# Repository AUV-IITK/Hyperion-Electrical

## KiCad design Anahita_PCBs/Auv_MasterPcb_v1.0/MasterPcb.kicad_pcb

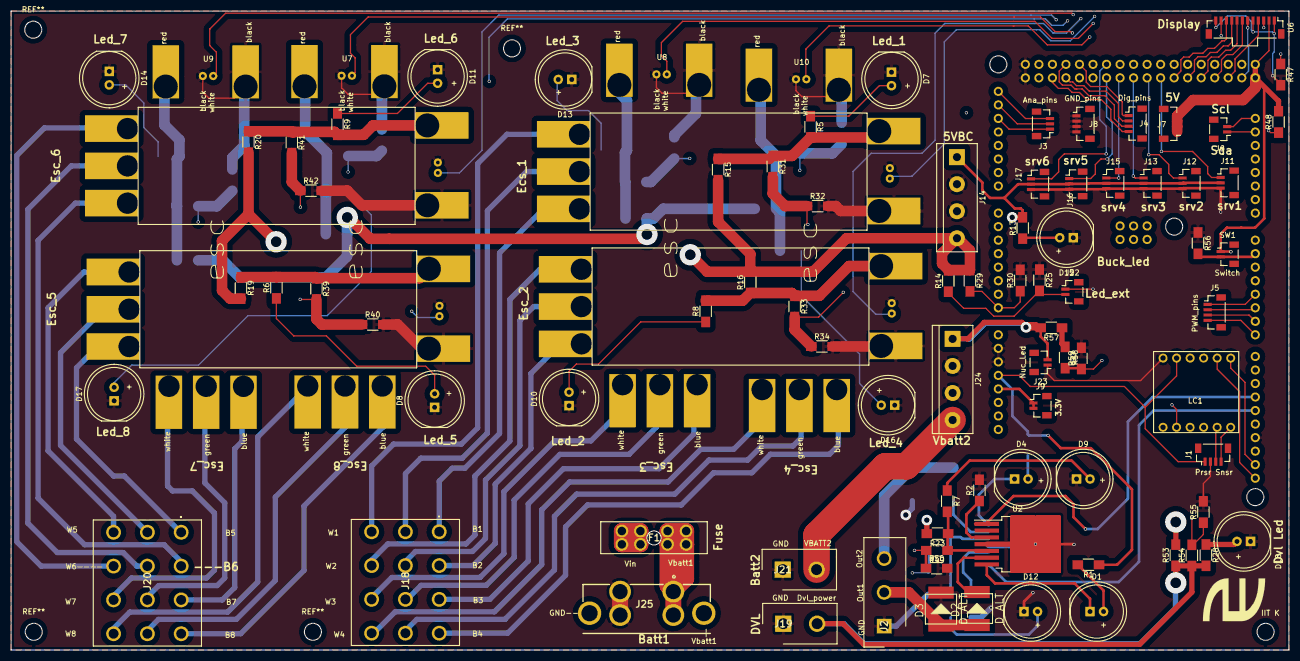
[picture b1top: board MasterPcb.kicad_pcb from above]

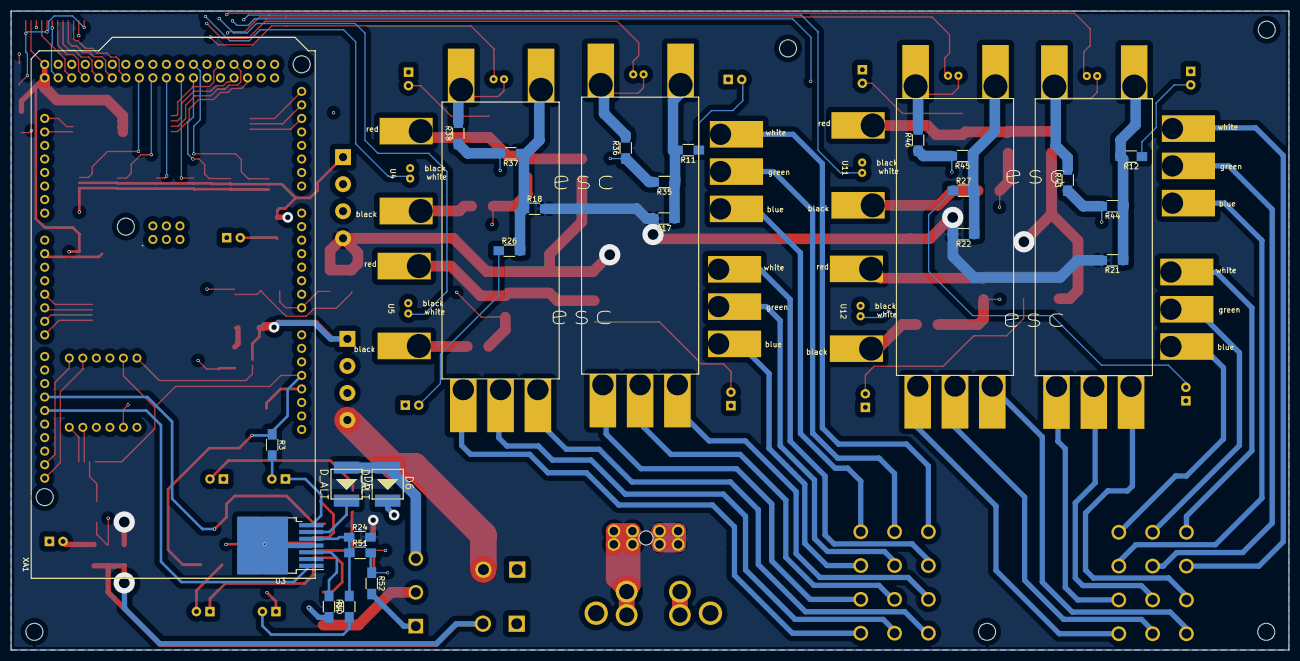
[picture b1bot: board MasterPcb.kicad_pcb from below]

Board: 4 copper layers, 240.0 x 120.0 mm, 118 parts (30 on the bottom side), 122 nets.

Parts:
D1, D4, D7, D8, D9, D10, D11, D12, D13, D14, D15, D16, D17, D18: LED; LED_D10.0mm
D2, D3, D5, D6: D_ALT; DO-214AB
F1: Fuse
IIT K: LOGO; logo
IIT K#2: M1; MountingHole_3.2mm_M3_DIN965
J1: Conn_02x02_Counter_Clockwise; Molex_PicoClasp_501331-0407_1x04_P1.0mm_Vertical
J2: conn_01x03; 1_3 pin&socket
J3: Conn_01x03_Male; Molex_PicoClasp_501331-0307_1x03_P1.0mm_Vertical
J4, J5, J7, J8: Conn_01x04_Male; Molex_PicoClasp_501331-0407_1x04_P1.0mm_Vertical
J6, J9: Conn_01x02_Male; Molex_PicoClasp_501331-0207_1x02_P1.0mm_Vertical
J11, J12, J13, J15, J16, J17: Conn_01x03_servo; Molex_PicoClasp_501331-0307_1x03_P1.0mm_Vertical
J14: Conn_01x04_5V_buckconverter; TerminalBlock_bornier-4_P5.08mm
J18, J20: Conn_01x12; 4_3connector
J19: Conn_01x02_Male_dvl; 1x2_Conn_
J21: Conn_01x02_power_nuc; 1x2_Conn_
J22: Led_ext_conn; Molex_PicoClasp_501331-0207_1x02_P1.0mm_Vertical
J23: Led_ext_nuc_conn; Molex_PicoClasp_501331-0207_1x02_P1.0mm_Vertical
J24: Conn_01x04_nuc_buck; TerminalBlock_bornier-4_P5.08mm
J25: Conn_01x04_power; power
LC1: Logic_Converter
R1, R3: 5K; R_1206_HandSoldering
R2, R4: 4K; R_1206_HandSoldering
R5, R6, R7, R8, R9, R10, R11, R12, R13, R26, R27, R28, R30, R32, R34, R36, R38, R40, R42, R43, R46, R47, R50, R52, R55, R56, R59: 1K; R_1206_HandSoldering
R14: 1k; R_1206_HandSoldering
R15, R16, R17, R18, R19, R20, R21, R22, R23, R24, R53, R57: 50m; R_1206_HandSoldering
R25: 4k; R_1206_HandSoldering
R29, R31, R33, R35, R37, R39, R41, R44, R45, R49, R51, R54, R58: 24K; R_1206_HandSoldering
R48: 220; R_1206_HandSoldering
SW1: SW_DIP_x01; Molex_PicoClasp_501331-0207_1x02_P1.0mm_Vertical
U2, U3: DRV102-RESCUE-Actuator_board; TO-263-7_TabPin4
U4, U5, U11, U12: ESCPINS; esc_redefined
U6: DS1; Molex_PicoClasp_501331-1207_1x12_P1.0mm_Vertical
U7, U8, U9, U10: ESCPINS; esc_mirror_redefined
XA1: Arduino_Mega2560_Shield

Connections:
/3.3V: J9.1, J9.2, LC1.8, XA1.3V3
/5V: J1.1, J7.1, J7.2, J7.3, J7.4, LC1.2, R1.1, R3.1, R48.2, SW1.1, U6.2, XA1.5V1, XA1.5V3, XA1.5V4
/5VBC: J11.2, J12.2, J13.2, J14.1, J15.2, J16.2, J17.2, R13.2
/22: U6.6, XA1.D22
/24: U6.4, XA1.D24
/26: U6.7, XA1.D26
/28: U6.8, XA1.D28
/30: U6.9, XA1.D30
/32: U6.10, XA1.D32
/A0: R29.2, R30.1, XA1.A0
/A1: R31.2, R32.1, XA1.A1
/A2: R33.2, R34.1, XA1.A2
/A3: R35.2, R36.1, XA1.A3
/A4: R37.2, R38.1, XA1.A4
/A5: R39.2, R40.1, XA1.A5
/A6: R41.2, R42.1, XA1.A6
/A7: R43.1, R44.2, XA1.A7
/A8: R45.2, R46.1, XA1.A8
/A9: R49.2, R50.1, XA1.A9
/A10: R51.2, R52.1, XA1.A10
/A11: R54.2, R55.1, XA1.A11
/A12: R58.2, R59.1, XA1.A12
/ANA1: J3.1, XA1.A13
/ANA2: J3.2, XA1.A14
/ANA3: J3.3, XA1.A15
/B1: J18.1, U4.1
/B2: J18.4, U5.1
/B3: J18.7, U8.1
/B4: J18.10, U10.1
/B5: J20.1, U12.1
/B6: J20.4, U11.1
/B7: J20.7, U9.1
/B8: J20.10, U7.1
/DIG1: J4.1, XA1.D47
/DIG2: J4.2, XA1.D48
/DIG3: J4.3, XA1.D49
/DIG4: J4.4, XA1.D50
/DVL: J19.2, R28.2, R53.1, R54.1
/G1: J18.2, U4.2
/G2: J18.5, U5.2
/G3: J18.8, U8.2
/G4: J18.11, U10.2
/G5: J20.2, U12.2
/G6: J20.5, U11.2
/G7: J20.8, U9.2
/G8: J20.11, U7.2
/IN_1: U2.1, XA1.D11
/IN_2: U3.1, XA1.D12
/Led_ext: J22.2, R14.1, R25.2
/Led_ext_nuc: J23.2, J24.1, R57.2
/NUC: R57.1, R58.1
/OUT_1: D2.1, D3.1, J2.2
/OUT_2: D5.1, D6.1, J2.3
/PWM-1: J5.1, XA1.D4
/PWM-2: J5.2, XA1.D5
/PWM-3: J5.3, XA1.D6
/PWM-4: J5.4, XA1.D7
/SCL1: J6.2, XA1.D21
/SCL(HV): LC1.5, XA1.SCL
/SCL(PS): J1.3, LC1.11
/SDA1: J6.1, XA1.D20
/SDA(HV): LC1.6, XA1.SDA
/SDA(PS): J1.4, LC1.12
/SER1: J11.1, XA1.D34
/SER2: J12.1, XA1.D36
/SER3: J13.1, XA1.D38
/SER4: J15.1, XA1.D40
/SER5: J16.1, XA1.D42
/SER6: J17.1, XA1.D43
/SOV1: R7.2, R23.1, R49.1, U2.5
/SOV2: R10.2, R24.1, R51.1, U3.5
/T-1: U4.4, XA1.D23
/T-2: U5.4, XA1.D25
/T-3: U8.4, XA1.D27
/T-4: U10.4, XA1.D29
/T-5: U12.4, XA1.D31
/T-6: U11.4, XA1.D33
/T-7: U9.4, XA1.D35
/T-8: U7.4, XA1.D37
/Trigger: R56.2, SW1.2, XA1.D1
/VBATT1: F1.1, F1.2, F1.3, F1.4, J25.1, J25.2
/VBATT2: J21.2, J24.4
/VESC1: R5.2, R15.1, R31.1, U4.6
/VESC2: R8.2, R16.1, R33.1, U5.6
/VESC3: R11.2, R17.1, R35.1, U8.6
/VESC4: R18.1, R26.2, R37.1, U10.6
/VESC5: R6.2, R19.1, R39.1, U12.6
/VESC6: R9.2, R20.1, R41.1, U11.6
/VESC7: R12.2, R21.1, R44.1, U9.6
/VESC8: R22.1, R27.2, R45.1, U7.6
/VIN1: F1.5, F1.6, F1.7, F1.8, J14.4, R14.2, R15.2, R16.2, R17.2, R18.2, R19.2, R20.2, R21.2, R22.2, R23.2, R24.2, R29.1, R53.2
/W1: J18.3, U4.3
/W2: J18.6, U5.3
/W3: J18.9, U8.3
/W4: J18.12, U10.3
/W5: J20.3, U12.3
/W6: J20.6, U11.3
/W7: J20.9, U9.3
/W8: J20.12, U7.3
GND: D3.2, D6.2, D7.1, D8.1, D9.1, D10.1, D11.1, D12.1, D13.1, D14.1, D15.1, D16.1, D17.1, D18.1, J1.2, J2.1, J8.1, J8.2, J8.3, J8.4, J11.3, J12.3, J13.3, J14.2, J14.3, J15.3, J16.3, J17.3, J19.1, J21.1, J22.1, J23.1, J24.2, J24.3, J25.3, J25.4, LC1.1, R2.2, R4.2, R25.1, R30.2, R32.2, R34.2, R36.2, R38.2, R40.2, R42.2, R43.2, R46.2, R47.2, R50.2, R52.2, R55.2, R56.1, R59.2, U2.4, U3.4, U4.5, U4.7, U5.5, U5.7, U6.1, U6.5, U6.12, U7.5, U7.7, U8.5, U8.7, U9.5, U9.7, U10.5, U10.7, U11.5, U11.7, U12.5, U12.7, XA1.GND1, XA1.GND2, XA1.GND3, XA1.GND5, XA1.GND6
unnamed: D1.1, U2.7
unnamed: D1.2, R1.2
unnamed: D2.2, U2.6
unnamed: D4.1, U3.7
unnamed: D4.2, R3.2
unnamed: D5.2, U3.6
unnamed: D7.2, R5.1
unnamed: D8.2, R6.1
unnamed: D9.2, R7.1
unnamed: D10.2, R8.1
unnamed: D11.2, R9.1
unnamed: D12.2, R10.1
unnamed: D13.2, R11.1
unnamed: D14.2, R12.1
unnamed: D15.2, R13.1
unnamed: D16.2, R26.1
unnamed: D17.2, R27.1
unnamed: D18.2, R28.1
unnamed: R2.1, U2.3
unnamed: R4.1, U3.3
unnamed: R47.1, U6.3
unnamed: R48.1, U6.11

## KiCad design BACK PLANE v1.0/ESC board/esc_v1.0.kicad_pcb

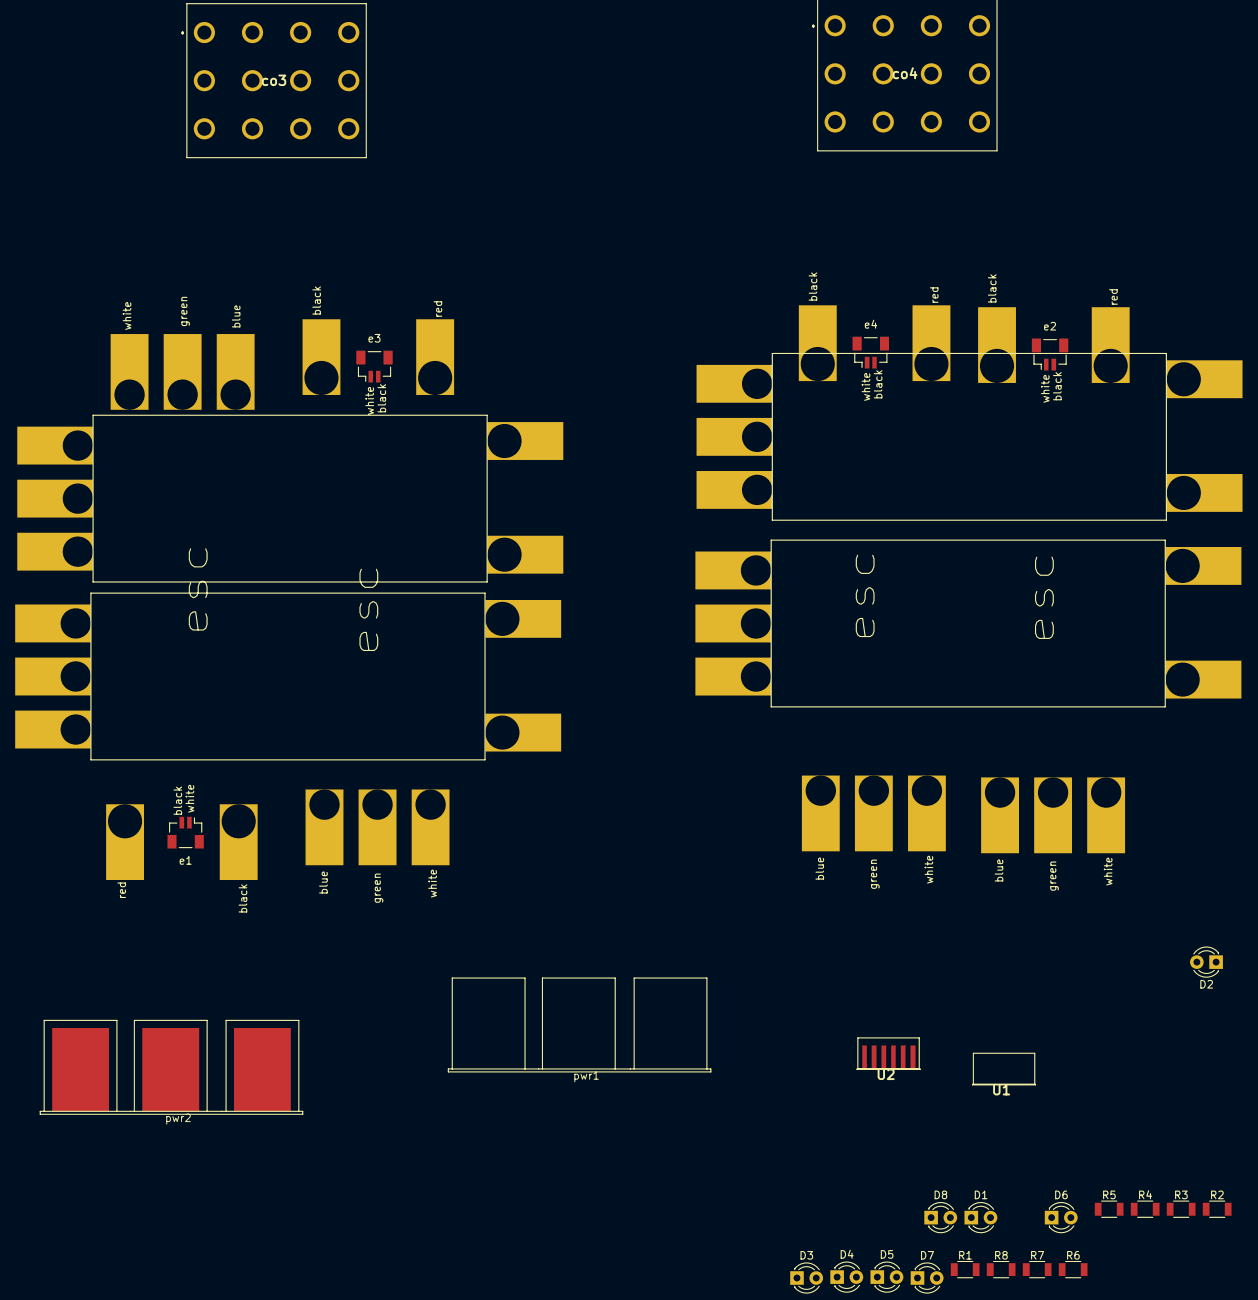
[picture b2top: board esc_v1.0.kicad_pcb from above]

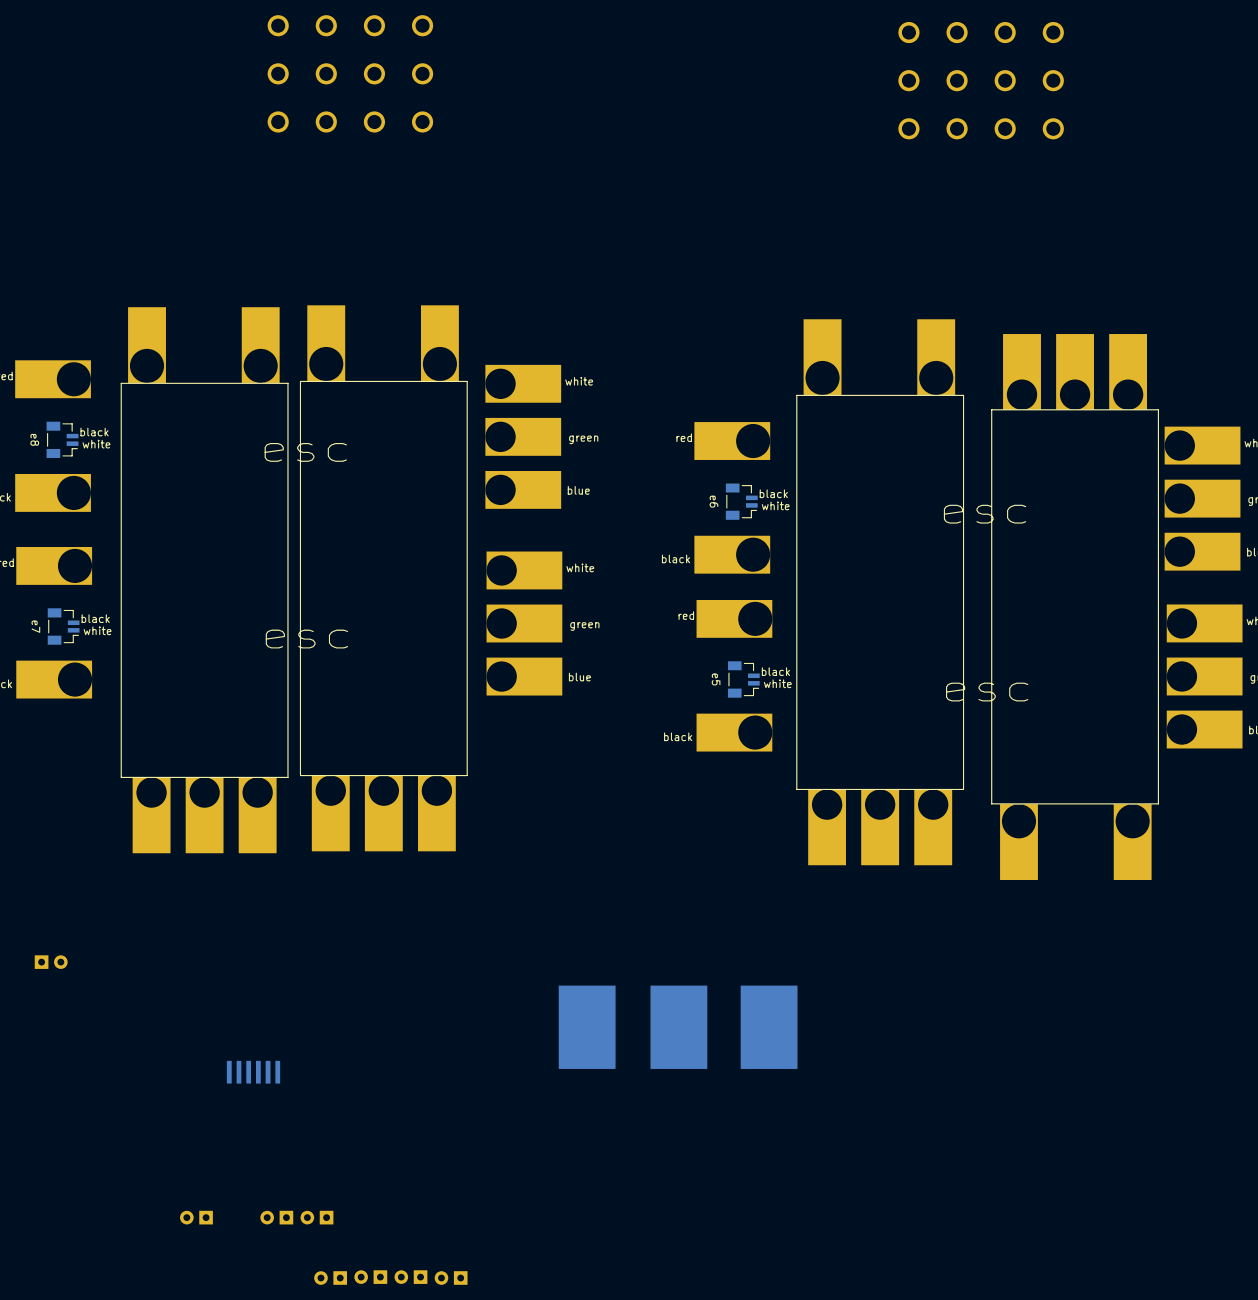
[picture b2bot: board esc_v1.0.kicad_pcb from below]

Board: 2 copper layers, 30 parts (4 on the bottom side), 43 nets, no tracks yet.

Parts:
D1, D2, D3, D4, D5, D6, D7, D8: LED; LED_D3.0mm
R1, R2, R3, R4, R5, R6, R7, R8: R; R_1206
U1: 6pin; edge card 0.65mm selfmade mirrored
U2: 6pin; edge card 0.65mm selfmade
co3, co4: 12_pin_conn; 4_3connector
e1, e2, e3, e4, e5, e6, e7, e8: esc
pwr1: 3pin; esc_power_3pin mirror
pwr2: 3pin; esc_power_3pin02

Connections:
/GND: R1.1, R2.1, R3.1, R4.1, R5.1, R6.1, R7.1, R8.1, e1.7, e2.7, e3.7, e4.7, e5.7, e6.7, e7.7, e8.7, pwr1.1, pwr1.2, pwr1.3
/VCC: D1.2, D2.2, D3.2, D4.2, D5.2, D6.2, D7.2, D8.2, e1.6, e2.6, e3.6, e4.6, e5.6, e6.6, e7.6, e8.6, pwr2.1, pwr2.2, pwr2.3
/ard_gnd: U2.6, e1.5, e2.5, e3.5, e4.5, e5.5, e6.5, e7.5, e8.5
/b1: co3.1, e1.1
/b2: co3.4, e2.1
/b3: co3.7, e3.1
/b4: co3.10, e4.1
/b5: co4.1, e5.1
/b6: co4.4, e6.1
/b7: co4.7, e7.1
/b8: co4.10, e8.1
/g1: co3.2, e1.2
/g2: co3.5, e2.2
/g3: co3.8, e3.2
/g4: co3.11, e4.2
/g5: co4.2, e5.2
/g6: co4.5, e6.2
/g7: co4.8, e7.2
/g8: co4.11, e8.2
/spd1: U1.1, e1.4
/spd2: U1.2, e2.4
/spd3: U1.3, e3.4
/spd4: U1.4, e4.4
/spd5: U1.5, e5.4
/spd6: U1.6, e6.4
/spd7: U2.1, e7.4
/spd8: U2.2, e8.4
/w1: co3.3, e1.3
/w2: co3.6, e2.3
/w3: co3.9, e3.3
/w4: co3.12, e4.3
/w5: co4.3, e5.3
/w6: co4.6, e6.3
/w7: co4.9, e7.3
/w8: co4.12, e8.3
unnamed: D1.1, R1.2
unnamed: D2.1, R2.2
unnamed: D3.1, R3.2
unnamed: D4.1, R4.2
unnamed: D5.1, R5.2
unnamed: D6.1, R6.2
unnamed: D7.1, R7.2
unnamed: D8.1, R8.2

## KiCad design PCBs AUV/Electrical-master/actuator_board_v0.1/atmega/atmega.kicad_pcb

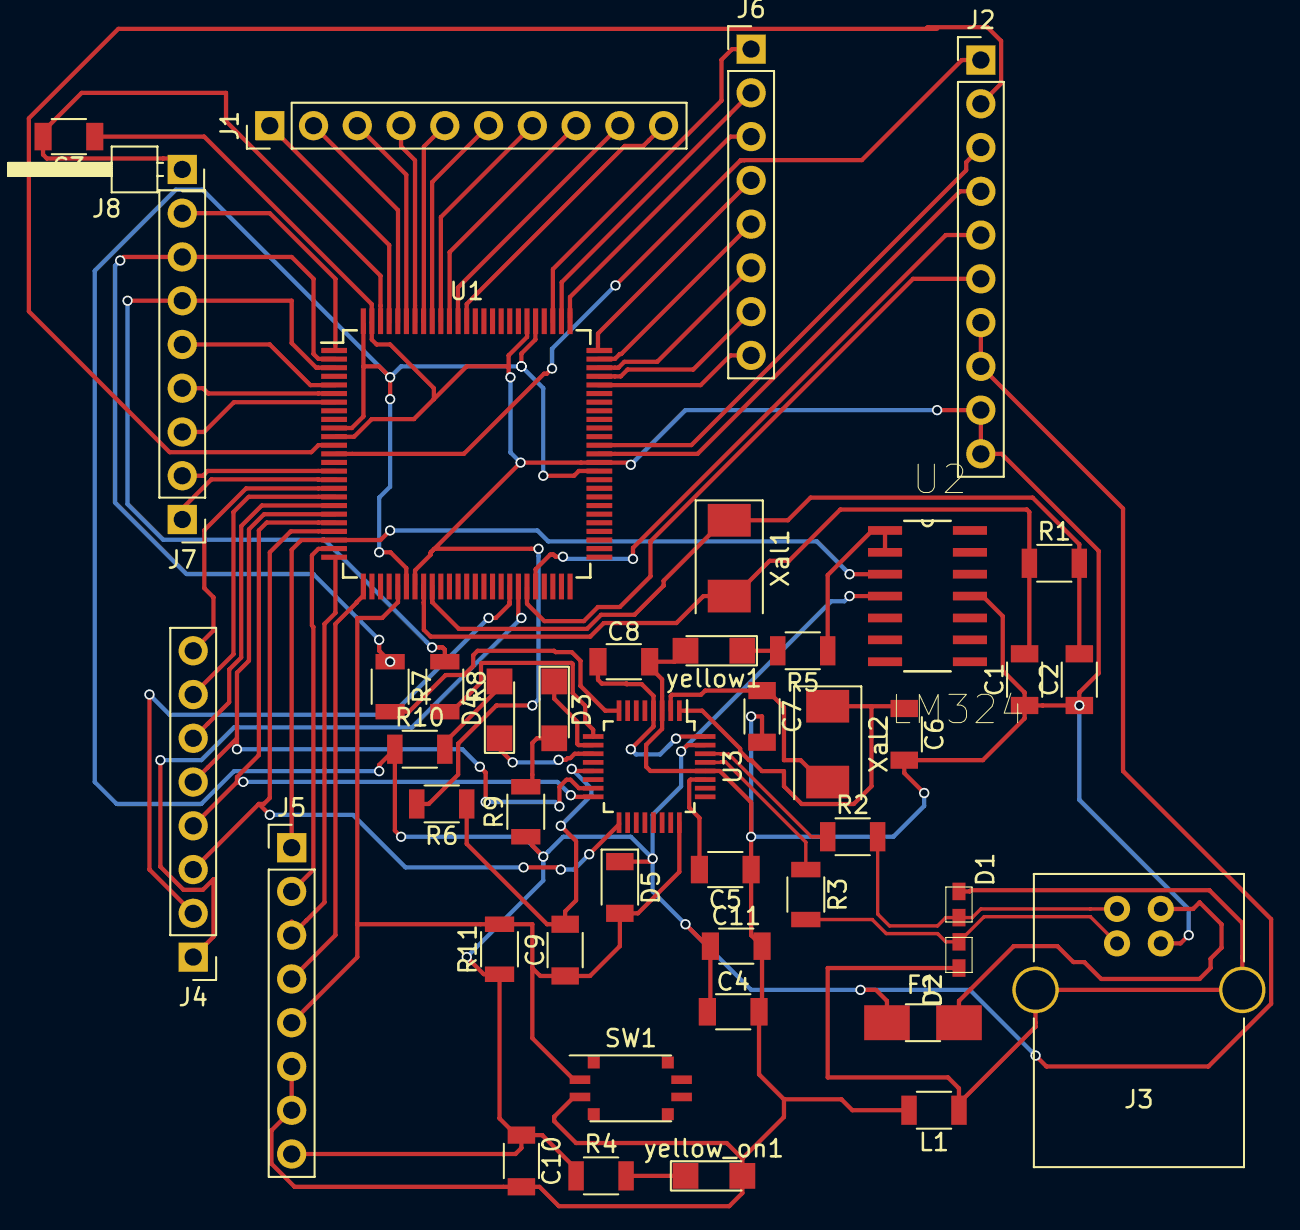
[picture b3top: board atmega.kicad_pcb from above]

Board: 2 copper layers, 45 parts (0 on the bottom side), 70 nets.

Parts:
C1, C2, C6, C7: 22pF; C_1206
C3, C4, C5, C8, C9, C10, C11: 100nF; C_1206
D1, D2: D_TVS; CG0603
D3, D4: LED; LED_1206
D5: D; D_1206
F1: Fuse; Fuse_SMD1206_HandSoldering
J1: Analog pins; Pin_Header_Straight_1x10_Pitch2.54mm
J2: CONN_01X10; Pin_Header_Straight_1x10_Pitch2.54mm
J3: USB_B
J4, J5, J6, J7: CONN_01X08; Pin_Header_Straight_1x08_Pitch2.54mm
J8: CONN_01X01; Pin_Header_Angled_1x01_Pitch2.54mm
L1: Ferrite_Bead; R_1206
R1: 1M; R_1206
R2, R3: 22R; R_1206
R4, R5, R6, R7, R8, R9, R10: 1k; R_1206
R11: 10k; R_1206
SW1: SW_Push; SW_DIP_x2_W5.9mm_Slide_Copal_CVS
U1: ATMEGA2560-8AU; TQFP-100_14x14mm_Pitch0.5mm
U2: LM324; SOIC127P600X175-14N
U3: ATMEGA16U2-AU; LQFP-32_5x5mm_Pitch0.5mm
Xal1, Xal2: 16MHz; Crystal_SMD_0603-2pin_6.0x3.5mm
yellow1: LED; LED_1206
yellow_on1: LED; LED_1206

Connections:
/AREF: C3.2, J8.1, U1.98
/AVCC: C8.1, U3.4, U3.32
/D+: R3.1, U3.29
/D-: R2.1, U3.30
/MISO: J4.3, U1.22, U3.17
/MOSI: J4.4, U1.21, U3.16
/PA0: J6.1, U1.78
/PA1: J6.2, U1.77
/PA2: J6.3, U1.76
/PA3: J6.4, U1.75
/PA4: J6.5, U1.74
/PA5: J6.6, U1.73
/PA6: J6.7, U1.72
/PA7: J6.8, U1.71
/PE3: J7.5, U1.5
/PE4: J7.4, U1.6
/PE5: J7.3, U1.7
/PG5: J7.8, U1.1
/PH3: J7.2, U1.15
/PH4: J7.1, U1.16
/RD+: D2.1, J3.3, R3.2
/RD-: D1.1, J3.2, R2.2
/RESET: C9.1, D5.2, J5.5, R11.2, SW1.1, U1.30, U3.24
/RX0: J7.7, R7.1, U1.2
/RXD1: J2.5, U1.46
/RXD2: J2.2, U1.12
/RXD3: J2.4, U1.63
/SCK: J4.5, U1.20, U3.15
/SCL: J4.2, U1.43
/SDA: J4.1, U1.44
/SHIELD: D1.2, D2.2, J3.5, L1.1
/SS: J4.6, U1.19
/TX0: J7.6, R8.1, U1.3
/TXD1: J2.6, U1.45
/TXD2: J2.1, U1.13
/TXD3: J2.3, U1.64
/UCAP: C5.2, U3.27
/a0: J1.8, U1.90
/a1: J1.7, U1.91
/a2: J1.6, U1.92
/a3: J1.5, U1.93
/a4: J1.4, U1.94
/a5: J1.3, U1.95
/a6: J1.2, U1.96
/a7: J1.1, U1.97
/a8: J1.10, U1.88
/a9: J1.9, U1.89
/p1: J5.1, U1.23, U2.3
/p2: J5.2, U1.24
/p3: J5.3, U1.25
/p4: J5.4, U1.26
/p5: J4.8, U1.17
/p6: J4.7, U1.18
GND: C1.1, C2.1, C3.1, C4.2, C5.1, C6.2, C7.2, C8.2, C10.2, C11.2, J2.9, J2.10, J3.4, J5.6, J5.7, L1.2, R6.2, SW1.2, U1.11, U1.32, U1.62, U1.81, U1.99, U2.11, U3.3, U3.28, yellow1.2, yellow_on1.2
unnamed: C1.2, R1.1, U1.33, Xal1.2
unnamed: C2.2, R1.2, U1.34, Xal1.1
unnamed: C6.1, U3.1, Xal2.1
unnamed: C7.1, U3.2, Xal2.2
unnamed: C9.2, R6.1, U3.13
unnamed: D3.1, U3.10
unnamed: D3.2, R9.2
unnamed: D4.1, U3.11
unnamed: D4.2, R10.2
unnamed: F1.2, J3.1
unnamed: R4.2, yellow_on1.1
unnamed: R5.1, U2.1, U2.2
unnamed: R5.2, yellow1.1
unnamed: R7.2, U3.8
unnamed: R8.2, U3.9
VCC: C4.1, C10.1, C11.1, D5.1, F1.1, J2.7, J2.8, J5.8, R4.1, R9.1, R10.1, R11.1, U1.10, U1.31, U1.61, U1.80, U1.100, U2.4, U3.31

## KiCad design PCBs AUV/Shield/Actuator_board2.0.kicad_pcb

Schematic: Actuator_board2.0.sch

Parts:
J1: Conn_01x05_Male; Pin_Header_Straight_1x05_Pitch2.54mm
J2, J3: Conn_01x13_Female; Socket_Strip_Straight_1x13_Pitch2.54mm
J4, J5, J8, J9, J12: Conn_01x04_Male; Pin_Header_Straight_1x04_Pitch2.54mm
J6: Conn_01x08_Male; Pin_Header_Straight_1x08_Pitch2.54mm
J7: Conn_01x07_Male; Pin_Header_Straight_1x07_Pitch2.54mm
J10, J11: Conn_01x02_Male; Pin_Header_Straight_1x02_Pitch2.54mm
XA1: Arduino_Mega2560_Shield

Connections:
/3.3V: J1.5, J11.1, J11.2, XA1.3V3 (3.3V)
/5V: J1.3, J4.1, J4.2, J4.3, J4.4, XA1.5V1 (5V)
/ANA1: J12.1, XA1.A4
/ANA2: J12.2, XA1.A5
/ANA3: J12.3, XA1.A6
/ANA4: J12.4, XA1.A7
/CS-1: J2.3, XA1.A0
/CS-2: J2.10, XA1.A1
/CS-3: J3.3, XA1.A2
/CS-4: J3.10, XA1.A3
/DIG1: J8.1, XA1.D40
/DIG2: J8.2, XA1.D41
/DIG3: J8.3, XA1.D42
/DIG4: J8.4, XA1.D43
/DIRA-1: J2.5, XA1.D22
/DIRA-2: J2.12, XA1.D24
/DIRA-3: J3.5, XA1.D26
/DIRA-4: J3.12, XA1.D28
/DIRB-1: J2.6, XA1.D23
/DIRB-2: J2.13, XA1.D25
/DIRB-3: J3.6, XA1.D27
/DIRB-4: J3.13, XA1.D29
/GND: J1.4, J2.1, J2.8, J3.1, J3.8, J5.1, J5.2, J5.3, J5.4, J6.2, J6.4, J6.6, J6.8, J7.7, XA1.GND1 (GND)
/PW1: J9.1, XA1.D6
/PW2: J9.2, XA1.D7
/PW3: J9.3, XA1.D8
/PW4: J9.4, XA1.D11
/PWM-1: J2.4, XA1.D2 (D2_INT0)
/PWM-2: J2.11, XA1.D3 (D3_INT1)
/PWM-3: J3.4, XA1.D4
/PWM-4: J3.11, XA1.D5
/S1: J7.1, XA1.D34
/S2: J7.2, XA1.D35
/S3: J7.3, XA1.D36
/S4: J7.4, XA1.D37
/S5: J7.5, XA1.D38
/S6: J7.6, XA1.D39
/SCL: J1.1, XA1.SCL
/SCL1: J10.2, XA1.D21 (D21_SCL)
/SDA: J1.2, XA1.SDA
/SDA1: J10.1, XA1.D20 (D20_SDA)
/T-5: J6.1, XA1.D30
/T-6: J6.3, XA1.D31
/T-7: J6.5, XA1.D32
/T-8: J6.7, XA1.D33

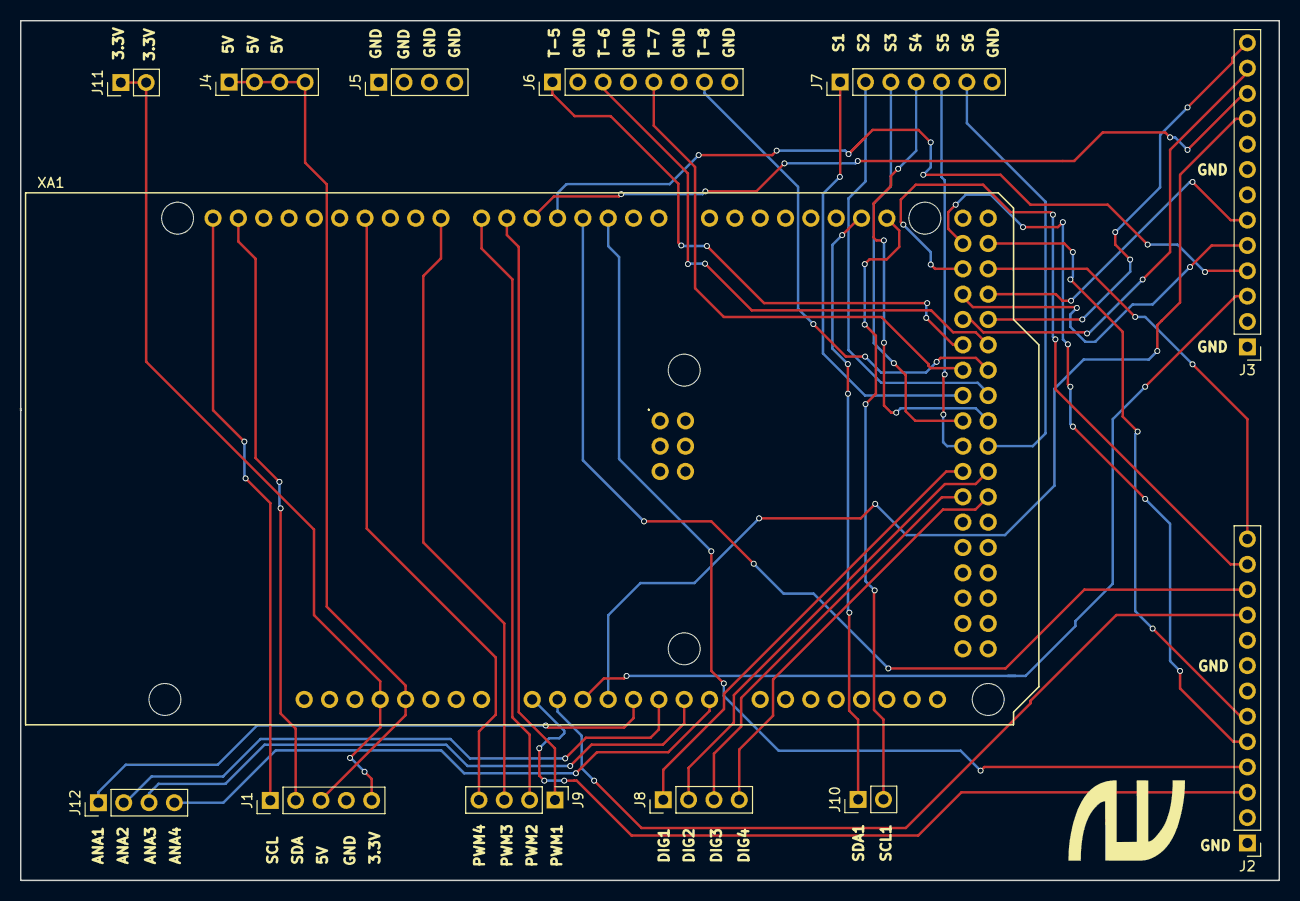
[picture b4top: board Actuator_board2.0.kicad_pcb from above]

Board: 2 copper layers, 126.2 x 86.2 mm, 13 parts (0 on the bottom side), 45 nets.
